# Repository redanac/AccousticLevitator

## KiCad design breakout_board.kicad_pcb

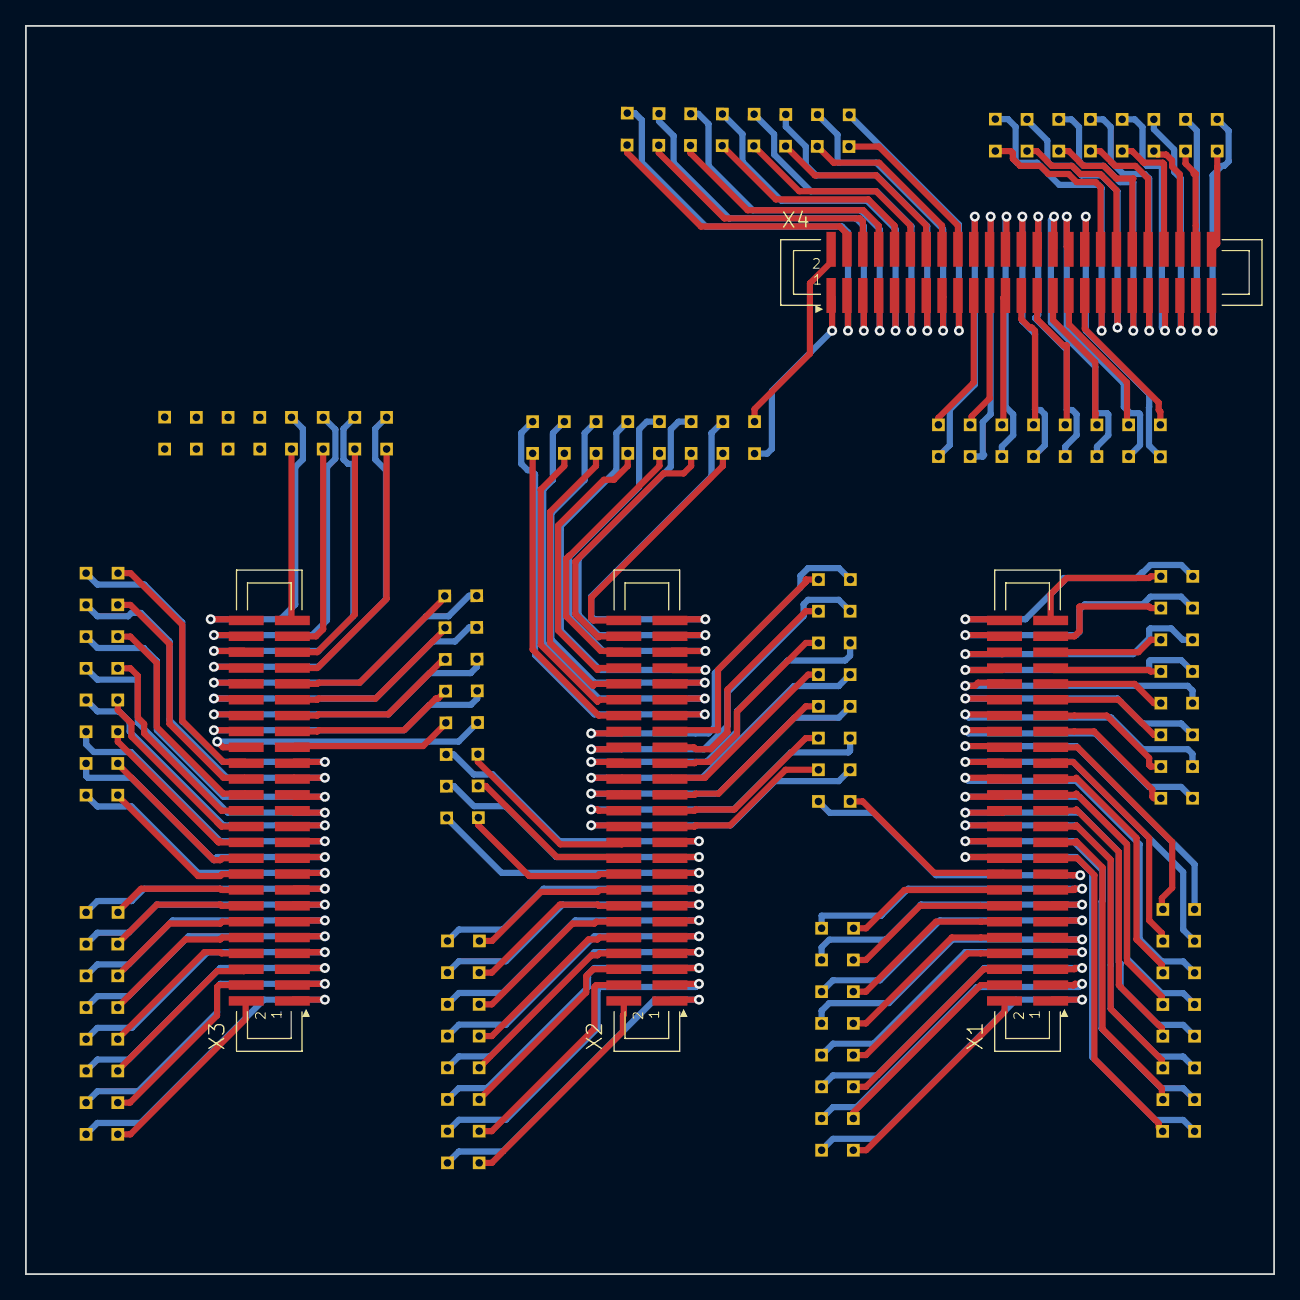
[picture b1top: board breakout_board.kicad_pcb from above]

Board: 2 copper layers, 100.0 x 100.0 mm, 17 parts (0 on the bottom side), 200 nets.

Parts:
C1, C2, C3, C4, C5, C6, C7, C8, C9, C10, C11, C12, C13: MOLEX_16_CONTACTSCONNECTOR; 16_CONTACT_MOLEX_CONNECTOR
X1, X2, X3, X4: PHB_1MM27_2X25_SNS

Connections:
/C101: C1.1, X4.1
/C102: C1.2, X4.2
/C103: C1.3, X2.50
/C104: C1.4, X2.49
/C105: C1.5, X2.48
/C106: C1.6, X2.47
/C107: C1.7, X2.46
/C108: C1.8, X2.45
/C109: C1.9, X2.44
/C110: C1.10, X2.43
/C111: C1.11, X2.42
/C112: C1.12, X2.41
/C113: C1.13, X2.40
/C114: C1.14, X2.39
/C115: C1.15, X2.38
/C116: C1.16, X2.37
/C201: C2.2, X1.20
/C202: C2.1, X1.19
/C203: C2.4, X1.22
/C204: C2.3, X1.21
/C205: C2.6, X1.24
/C206: C2.5, X1.23
/C207: C2.8, X1.26
/C208: C2.7, X1.25
/C209: C2.10, X1.28
/C210: C2.9, X1.27
/C211: C2.12, X1.30
/C212: C2.11, X1.29
/C213: C2.14, X1.32
/C214: C2.13, X1.31
/C215: C2.16, X1.34
/C216: C2.15, X1.33
/C301: C3.1, X3.32
/C302: C3.2, X3.31
/C303: C3.3, X3.30
/C304: C3.4, X3.29
/C305: C3.5, X3.28
/C306: C3.6, X3.27
/C307: C3.7, X3.26
/C308: C3.8, X3.25
/C309: C3.9, X3.24
/C310: C3.10, X3.23
/C311: C3.11, X3.22
/C312: C3.12, X3.21
/C313: C3.13, X3.20
/C314: C3.14, X3.19
/C315: C3.15, X3.18
/C316: C3.16, X3.17
/C401: C4.1, X1.50
/C402: C4.2, X1.49
/C403: C4.3, X1.48
/C404: C4.4, X1.47
/C405: C4.5, X1.46
/C406: C4.6, X1.45
/C407: C4.7, X1.44
/C408: C4.8, X1.43
/C409: C4.9, X1.42
/C410: C4.10, X1.41
/C411: C4.11, X1.40
/C412: C4.12, X1.39
/C413: C4.13, X1.38
/C414: C4.14, X1.37
/C415: C4.15, X1.36
/C416: C4.16, X1.35
/C501: C5.1, X2.16
/C502: C5.2, X2.15
/C503: C5.3, X2.14
/C504: C5.4, X2.13
/C505: C5.5, X2.12
/C506: C5.6, X2.11
/C507: C5.7, X2.10
/C508: C5.8, X2.9
/C509: C5.9, X2.8
/C510: C5.10, X2.7
/C511: C5.11, X2.6
/C512: C5.12, X2.5
/C513: C5.13, X2.4
/C514: C5.14, X2.3
/C515: C5.15, X2.2
/C516: C5.16, X2.1
/C601: C6.1, X3.16
/C602: C6.2, X3.15
/C603: C6.3, X3.14
/C604: C6.4, X3.13
/C605: C6.5, X3.12
/C606: C6.6, X3.11
/C607: C6.7, X3.10
/C608: C6.8, X3.9
/C609: C6.9, X3.8
/C610: C6.10, X3.7
/C611: C6.11, X3.6
/C612: C6.12, X3.5
/C613: C6.13, X3.4
/C614: C6.14, X3.3
/C615: C6.15, X3.2
/C616: C6.16, X3.1
/C701: C7.1, X2.36
/C702: C7.2, X2.35
/C703: C7.3, X2.34
/C704: C7.4, X2.33
/C705: C7.5, X2.32
/C706: C7.6, X2.31
/C707: C7.7, X2.30
/C708: C7.8, X2.29
/C709: C7.9, X2.28
/C710: C7.10, X2.27
/C711: C7.11, X2.26
/C712: C7.12, X2.25
/C713: C7.13, X2.24
/C714: C7.14, X2.23
/C715: C7.15, X1.18
/C716: C7.16, X1.17
/C809: C8.9, X3.50
/C810: C8.10, X3.49
/C811: C8.11, X3.48
/C812: C8.12, X3.47
/C813: C8.13, X3.46
/C814: C8.14, X3.45
/C815: C8.15, X3.44
/C816: C8.16, X3.43
/C901: C9.1, X4.34
/C902: C9.2, X4.33
/C903: C9.3, X4.32
/C904: C9.4, X4.31
/C905: C9.5, X4.30
/C906: C9.6, X4.29
/C907: C9.7, X4.28
/C908: C9.8, X4.27
/C909: C9.9, X4.26
/C910: C9.10, X4.25
/C911: C9.11, X4.24
/C912: C9.12, X4.23
/C913: C9.13, X4.22
/C914: C9.14, X4.21
/C915: C9.15, X4.20
/C916: C9.16, X4.19
/C1001: C10.1, X4.35
/C1002: C10.2, X4.36
/C1003: C10.3, X4.37
/C1004: C10.4, X4.38
/C1005: C10.5, X4.39
/C1006: C10.6, X4.40
/C1007: C10.7, X4.41
/C1008: C10.8, X4.42
/C1009: C10.9, X4.43
/C1010: C10.10, X4.44
/C1011: C10.11, X4.45
/C1012: C10.12, X4.46
/C1013: C10.13, X4.47
/C1014: C10.14, X4.48
/C1015: C10.15, X4.49
/C1016: C10.16, X4.50
/C1101: C11.1, X1.16
/C1102: C11.2, X1.15
/C1103: C11.3, X1.14
/C1104: C11.4, X1.13
/C1105: C11.5, X1.12
/C1106: C11.6, X1.11
/C1107: C11.7, X1.10
/C1108: C11.8, X1.9
/C1109: C11.9, X1.8
/C1110: C11.10, X1.7
/C1111: C11.11, X1.6
/C1112: C11.12, X1.5
/C1113: C11.13, X1.4
/C1114: C11.14, X1.3
/C1115: C11.15, X1.2
/C1116: C11.16, X1.1
/C1201: C12.1, X4.3
/C1202: C12.2, X4.4
/C1203: C12.3, X4.5
/C1204: C12.4, X4.6
/C1205: C12.5, X4.7
/C1206: C12.6, X4.8
/C1207: C12.7, X4.9
/C1208: C12.8, X4.10
/C1209: C12.9, X4.11
/C1210: C12.10, X4.12
/C1211: C12.11, X4.13
/C1212: C12.12, X4.14
/C1213: C12.13, X4.15
/C1214: C12.14, X4.16
/C1215: C12.15, X4.17
/C1216: C12.16, X4.18
/C1301: C13.1, X3.42
/C1302: C13.2, X3.41
/C1303: C13.3, X3.40
/C1304: C13.4, X3.39
/C1305: C13.5, X3.38
/C1306: C13.6, X3.37
/C1307: C13.7, X3.36
/C1308: C13.8, X3.35
/C1309: C13.9, X3.34
/C1310: C13.10, X3.33
/C1311: C13.11, X2.22
/C1312: C13.12, X2.21
/C1313: C13.13, X2.20
/C1314: C13.14, X2.19
/C1315: C13.15, X2.18
/C1316: C13.16, X2.17

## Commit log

2019-05-31 Add files via upload
    first draft for breakout boards
